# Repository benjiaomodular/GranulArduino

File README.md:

# GranulArduino

Find the full documentation on [my website](https://benjiaomodular.com/post/2022-03-31-granularduino/).

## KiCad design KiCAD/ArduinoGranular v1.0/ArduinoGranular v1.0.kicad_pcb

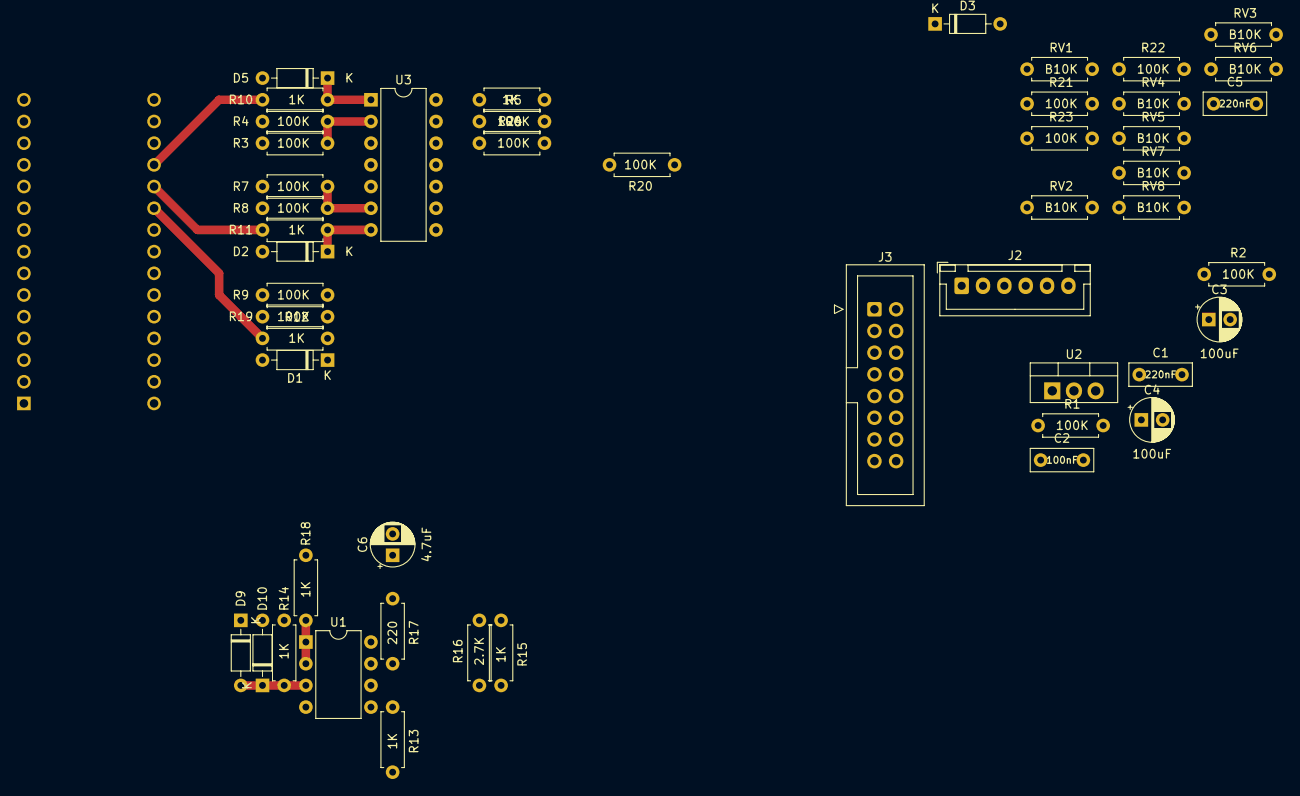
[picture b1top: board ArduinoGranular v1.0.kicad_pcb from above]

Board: 2 copper layers, 50 parts (1 on the bottom side), 37 nets.

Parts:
A1: Arduino_Nano_v3.x; Arduino_Nano
C1, C5: 220nF; Capacitor_Rect_L7.2mm_W2.5mm_P5.00mm
C2: 100nF; Capacitor_Rect_L7.2mm_W2.5mm_P5.00mm
C3, C4: 100uF; Capacitor_Radial_D5.0mm_P2.5mm
C6: 4.7uF; Capacitor_Radial_D5.0mm_P2.5mm
D1, D2, D3, D5, D9, D10: BAT43; D_DO-35_SOD27_P7.62mm_Horizontal
J2: JST_BUS; JST_XH_B6B-XH-A_1x06_P2.50mm_Vertical
J3: IDC_BUS; IDC-Header_2x08_P2.54mm_Vertical
R1, R2, R3, R4, R5, R6, R7, R8, R9, R19, R20, R21, R22, R23: 100K; Resistor_L6.3mm_D2.5mm_P7.62mm_Horizontal
R10, R11, R12, R13, R14, R15, R18, R24: 1K; Resistor_L6.3mm_D2.5mm_P7.62mm_Horizontal
R16: 2.7K; Resistor_L6.3mm_D2.5mm_P7.62mm_Horizontal
R17: 220; Resistor_L6.3mm_D2.5mm_P7.62mm_Horizontal
RV1, RV2, RV3, RV4, RV5, RV6, RV7, RV8: B10K; Resistor_L6.3mm_D2.5mm_P7.62mm_Horizontal
U1: TL072; DIP-8_W7.62mm
U2: L7805; TO-220-3_Vertical
U3: TL074; DIP-14_W7.62mm

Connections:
+5V: C2.1, D9.1, R1.2, RV1.1, RV2.1, RV3.1, RV4.1, U2.3
-12V: C4.2, J2.6, J3.1, J3.2, U1.4, U3.11
ARDUINO_OUTPUT: A1.6, R13.2
B2_12V: A1.30, C1.1, C3.1, J2.4, J3.9, J3.10, U1.8, U2.1, U3.4
GND: A1.4, A1.29, C5.2, D1.2, D2.2, D3.2, D5.2, D10.2, R2.1, R15.1
GND2: C1.2, C2.2, C3.2, C4.1, J2.5, J3.3, J3.4, J3.5, J3.6, J3.7, J3.8, U2.2
GRAIN1_DECAY: A1.20, R11.1
GRAIN1_FREQ: A1.19, R10.1
GRAIN2_DECAY: A1.22, R24.1
GRAIN2_FREQ: A1.21, R12.1
unnamed: C5.1, R13.1, U1.5
unnamed: C6.1, R17.1
unnamed: D1.1, R20.2, R24.2, U3.14
unnamed: D2.1, R11.2, R22.2, U3.7
unnamed: D3.1, R12.2, R23.2, U3.8
unnamed: D5.1, R10.2, R21.2, U3.1
unnamed: D9.2, D10.1, R14.1, U1.3
unnamed: J3.11, J3.12
unnamed: J3.13, J3.14
unnamed: J3.15, J3.16
unnamed: R3.2, RV6.2
unnamed: R4.2, RV2.2
unnamed: R5.2, RV5.2
unnamed: R6.2, RV1.2
unnamed: R7.2, RV7.2
unnamed: R8.2, RV3.2
unnamed: R9.2, RV8.2
unnamed: R15.2, R16.1, U1.6
unnamed: R16.2, R17.2, U1.7
unnamed: R18.2, U1.1, U1.2
unnamed: R9.1, R19.1, R23.1, U3.9
unnamed: R19.2, RV4.2
unnamed: R5.1, R6.1, R20.1, U3.12
unnamed: R3.1, R4.1, R21.1, U3.2
unnamed: R7.1, R8.1, R22.1, U3.6
SYNC: A1.23, R18.1
VREF: R1.1, R2.2, U3.3, U3.5, U3.10, U3.13

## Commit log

2022-03-30 ADded license and readme
2022-03-30 Marked NCs, fixed IDC bus grounds
2022-03-31 Renamed
2022-03-31 Added octave selector
